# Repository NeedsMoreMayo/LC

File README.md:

# LC meter
The LC meter in this project is based on a popular design that's found on numerous websites. I added an external GPSDO input to use as stable clock reference and a second input so the meter can be used as a frequency counter.

## Principle of operation

## Major components
- The display is a 1602A (ver 5.5) with an I2C PCF8574 expander from aliExpress.
- uC is AVR32DB28

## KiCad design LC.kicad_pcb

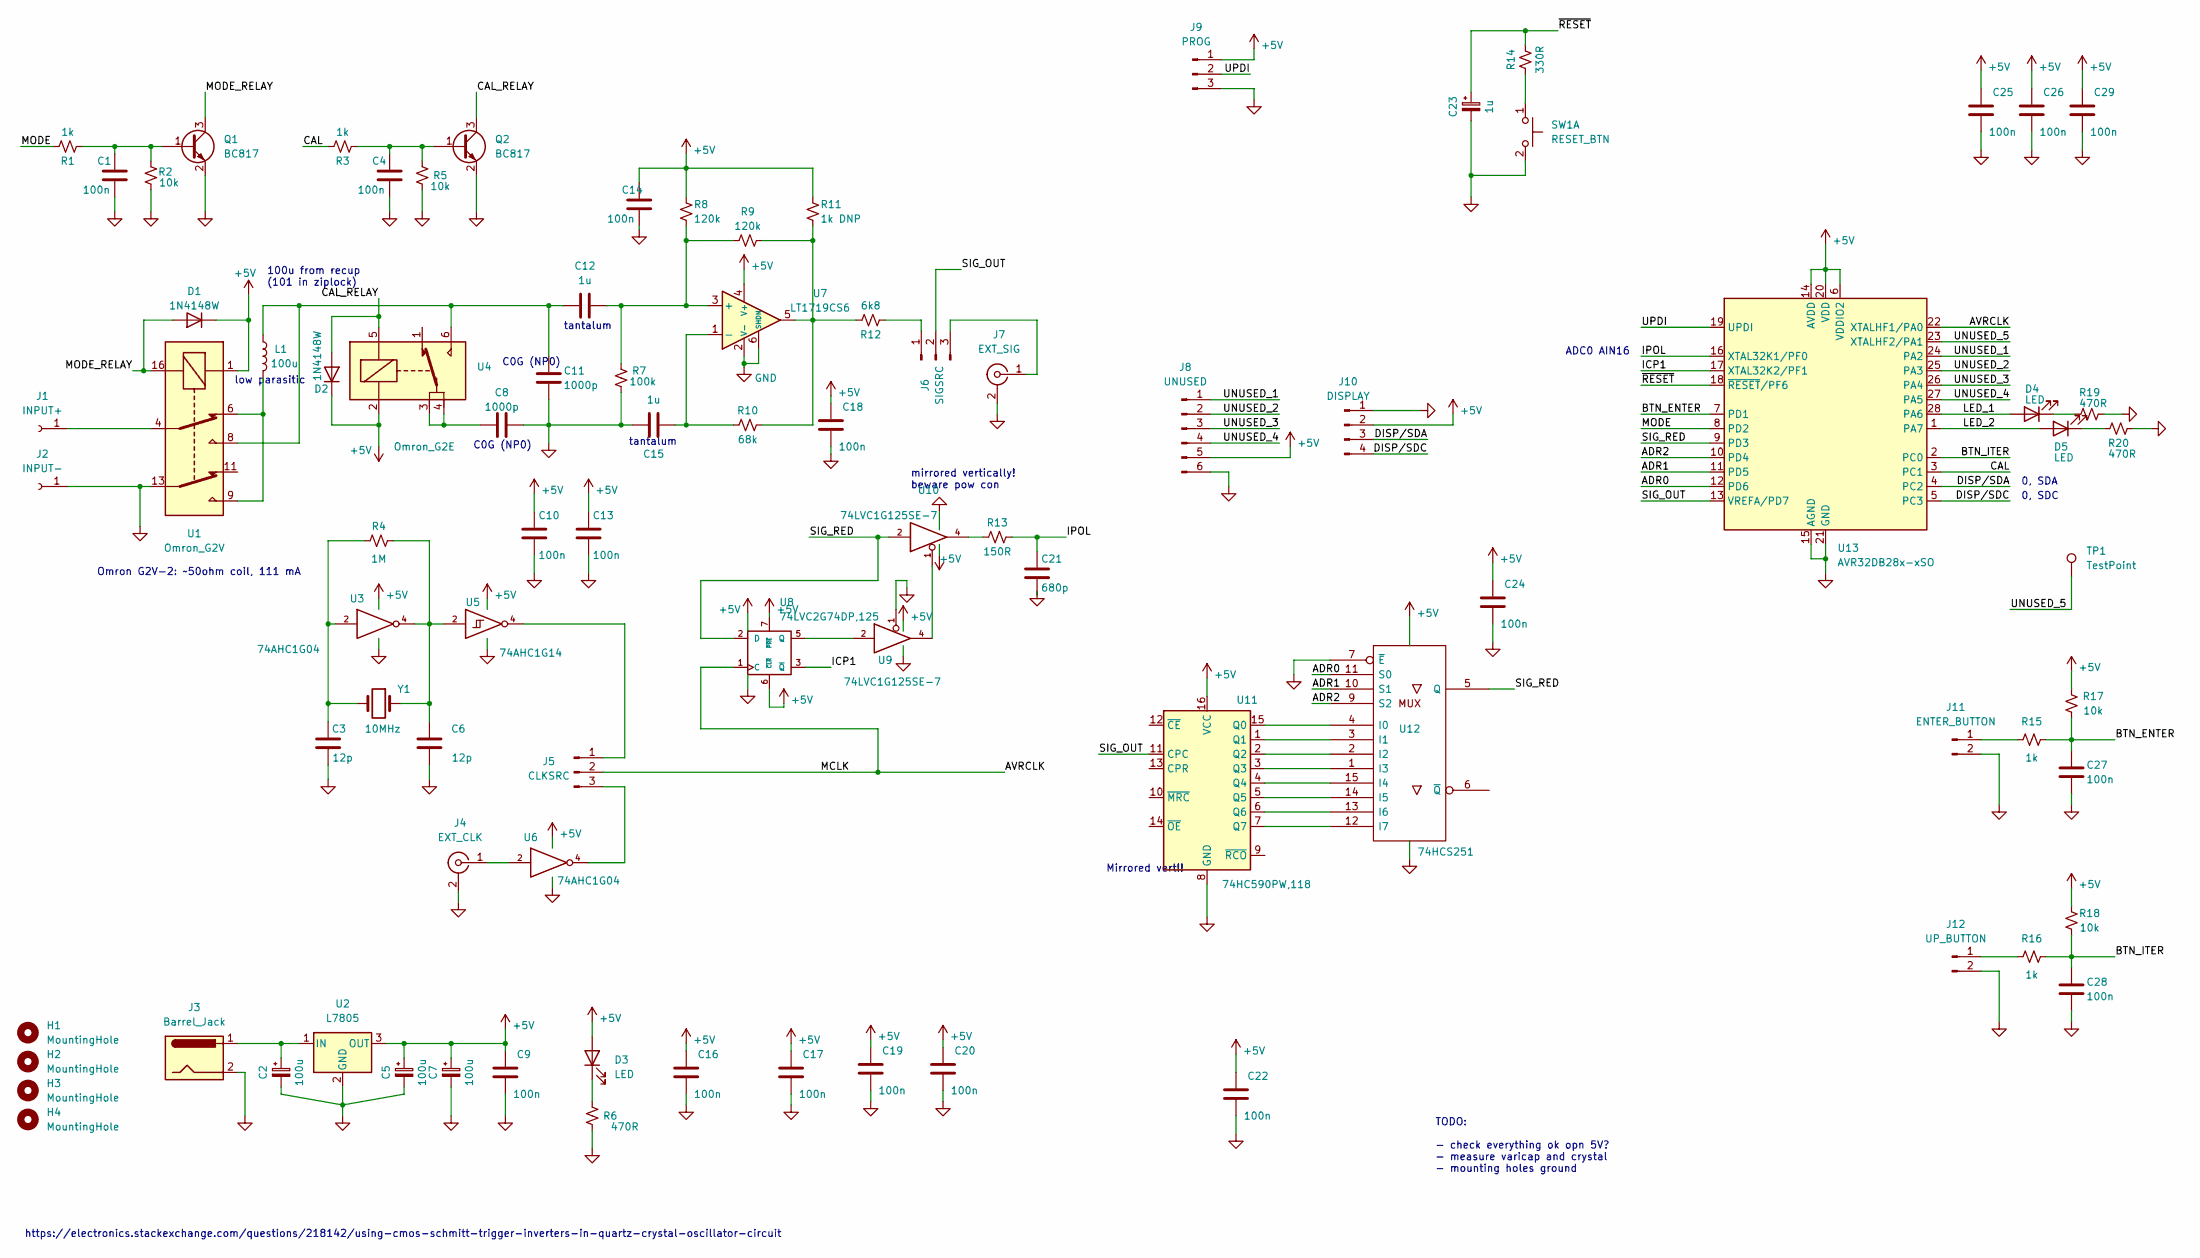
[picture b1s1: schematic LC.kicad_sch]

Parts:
C1, C4, C9, C10, C13, C14, C16, C17, C18, C19, C20, C22, C24, C25, C26, C27, C28, C29: 100n; C_0805_2012Metric_Pad1.18x1.45mm_HandSolder
C2, C5, C7: 100u; CP_Radial_D5.0mm_P2.00mm
C3, C6: 12p; C_0805_2012Metric_Pad1.18x1.45mm_HandSolder
C8, C11: 1000p; C_0805_2012Metric_Pad1.18x1.45mm_HandSolder
C12, C15, C23: 1u; C_0805_2012Metric_Pad1.18x1.45mm_HandSolder
C21: 680p; C_0805_2012Metric_Pad1.18x1.45mm_HandSolder
D1, D2: 1N4148W; D_SOD-123
D3, D4, D5: LED; LED_1206_3216Metric
H1, H2, H3, H4: MountingHole; MountingHole_3.2mm_M3_Pad
J1: INPUT+; Pin_D1.0mm_L10.0mm
J2: INPUT-; Pin_D1.0mm_L10.0mm
J3: Barrel_Jack; BarrelJack_GCT_DCJ200-10-A_Horizontal
J4: EXT_CLK; U.FL_Molex_MCRF_73412-0110_Vertical
J5: CLKSRC; PinHeader_1x03_P2.54mm_Vertical
J6: SIGSRC; PinHeader_1x03_P2.54mm_Vertical
J7: EXT_SIG; U.FL_Molex_MCRF_73412-0110_Vertical
J8: UNUSED; PinHeader_2x03_P2.54mm_Vertical
J9: PROG; PinHeader_1x03_P2.54mm_Vertical
J10: DISPLAY; PinHeader_1x04_P2.54mm_Vertical
J11: ENTER_BUTTON; PinHeader_1x02_P2.54mm_Vertical
J12: UP_BUTTON; PinHeader_1x02_P2.54mm_Vertical
L1: 100u; L_Coilcraft_LPS5030
Q1, Q2: BC817; SOT-23
R1, R3, R15, R16: 1k; R_0805_2012Metric_Pad1.20x1.40mm_HandSolder
R2, R5, R17, R18: 10k; R_0805_2012Metric_Pad1.20x1.40mm_HandSolder
R4: 1M; R_0805_2012Metric_Pad1.20x1.40mm_HandSolder
R6, R19, R20: 470R; R_0805_2012Metric_Pad1.20x1.40mm_HandSolder
R7: 100k; R_0805_2012Metric_Pad1.20x1.40mm_HandSolder
R8, R9: 120k; R_0805_2012Metric_Pad1.20x1.40mm_HandSolder
R10: 68k; R_0805_2012Metric_Pad1.20x1.40mm_HandSolder
R11: 1k DNP; R_0805_2012Metric_Pad1.20x1.40mm_HandSolder
R12: 6k8; R_0805_2012Metric_Pad1.20x1.40mm_HandSolder
R13: 150R; R_0805_2012Metric_Pad1.20x1.40mm_HandSolder
R14: 330R; R_0805_2012Metric_Pad1.20x1.40mm_HandSolder
SW1: RESET_BTN; BUTTON_5X5
TP1: TestPoint; TestPoint_THTPad_1.0x1.0mm_Drill0.5mm
U1: Omron_G2V; Omron G2V-2
U2: L7805; TO-220-3_Vertical
U3, U6: 74AHC1G04; SOT-23-5_HandSoldering
U4: Omron_G2E; Omron G2E
U5: 74AHC1G14; SOT-23-5_HandSoldering
U7: LT1719CS6; SOT-23-6
U8: 74LVC2G74DP,125; TSSOP-8_3x3mm_P0.65mm
U9, U10: 74LVC1G125SE-7; SOT-353_SC-70-5
U11: 74HC590PW,118; TSSOP-16_4.4x5mm_P0.65mm
U12: 74HCS251; SOIC-16_4.55x10.3mm_P1.27mm
U13: AVR32DB28x-xSO; SOIC-28W_7.5x17.9mm_P1.27mm
Y1: 10MHz; Crystal_HC49-4H_Vertical

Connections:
+5V: C5.1, C7.1, C9.2, C10.2, C13.2, C14.2, C16.2, C17.2, C18.2, C19.2, C20.2, C22.2, C24.2, C25.2, C26.2, C29.2, D1.1 (K), D2.1 (K), D3.2 (A), J8.5, J9.1, J10.2, R8.2, R11.2, R17.1, R18.1, U1.1, U2.3 (OUT), U3.5 (VCC), U4.2, U5.5 (VCC), U6.5 (VCC), U7.4 (V+), U8.6 (~CLR), U8.7 (~PRE), U8.8 (VCC), U9.5 (VCC), U10.5 (VCC), U11.16 (VCC), U12.16 (VCC), U13.6 (VDDIO2), U13.14 (AVDD), U13.20 (VDD)
/ADR0: U12.11 (S0), U13.12 (PD6)
/ADR1: U12.10 (S1), U13.11 (PD5)
/ADR2: U12.9 (S2), U13.10 (PD4)
/AVRCLK: J5.2, U8.1 (C), U13.22 (XTALHF1/PA0)
/BTN_ENTER: C27.2, R15.2, R17.2, U13.7 (PD1)
/BTN_ITER: C28.2, R16.2, R18.2, U13.2 (PC0)
/CAL: R3.2, U13.3 (PC1)
/CAL_RELAY: D2.2 (A), Q2.3 (C), U4.5
/DISP/SDA: J10.3, U13.4 (PC2)
/DISP/SDC: J10.4, U13.5 (PC3)
/ICP1: U8.3 (~Q), U13.17 (XTAL32K2/PF1)
/IPOL: C21.2, R13.1, U13.16 (XTAL32K1/PF0)
/LED_1: D4.2 (A), U13.28 (PA6)
/LED_2: D5.2 (A), U13.1 (PA7)
/MODE: R1.2, U13.8 (PD2)
/MODE_RELAY: D1.2 (A), Q1.3 (C), U1.16
/SIG_OUT: J6.2, U11.11 (CPC), U13.13 (VREFA/PD7)
/SIG_RED: U8.2 (D), U10.2, U12.5 (Q), U13.9 (PD3)
/UNUSED_1: J8.1, U13.24 (PA2)
/UNUSED_2: J8.2, U13.25 (PA3)
/UNUSED_3: J8.3, U13.26 (PA4)
/UNUSED_4: J8.4, U13.27 (PA5)
/UNUSED_5: TP1.1, U13.23 (XTALHF2/PA1)
/UPDI: J9.2, U13.19 (UPDI)
/~RESET: C23.1, R14.2, U13.18 (~RESET/PF6)
GND: C1.1, C2.2, C3.2, C4.1, C5.2, C6.2, C7.2, C8.1, C9.1, C10.1, C11.1, C13.1, C14.1, C15.1, C16.1, C17.1, C18.1, C19.1, C20.1, C21.1, C22.1, C23.2, C24.1, C25.1, C26.1, C27.1, C28.1, C29.1, J2.1, J3.2, J4.2 (Ext), J7.2 (Ext), J8.6, J9.3, J10.1, J11.2, J12.2, Q1.2 (E), Q2.2 (E), R2.2, R5.2, R6.2, R7.1, R19.2, R20.2, SW1.2 (D), U1.13, U2.2 (GND), U3.3 (GND), U5.3 (GND), U6.3 (GND), U7.2 (V-), U7.6 (SHDN), U8.4 (GND), U9.1, U9.3 (GND), U10.3 (GND), U11.8 (GND), U12.7 (~E), U12.8 (GND), U13.15 (AGND), U13.21 (GND)
unnamed: C1.2, Q1.1 (B), R1.1, R2.1
unnamed: C2.1, J3.1, U2.1 (IN)
unnamed: C3.1, R4.1, U3.2, Y1.2
unnamed: C4.2, Q2.1 (B), R3.1, R5.1
unnamed: C6.1, R4.2, U3.4, U5.2, Y1.1
unnamed: C8.2, U4.3, U4.4
unnamed: C11.2, C12.1, L1.1, U1.8, U4.6
unnamed: C12.2, R7.2, R8.1, R9.1, U7.3 (+)
unnamed: C15.2, R10.1, U7.1 (-)
unnamed: D3.1 (K), R6.1
unnamed: D4.1 (K), R19.1
unnamed: D5.1 (K), R20.1
unnamed: J1.1, U1.4
unnamed: J4.1 (In), U6.2
unnamed: J5.1, U5.4
unnamed: J5.3, U6.4
unnamed: J6.1, R12.1
unnamed: J6.3, J7.1 (In)
unnamed: J11.1, R15.1
unnamed: J12.1, R16.1
unnamed: L1.2, U1.6, U1.9
unnamed: R9.2, R10.2, R11.1, R12.2, U7.5
unnamed: R13.2, U10.4
unnamed: R14.1, SW1.1 (C)
unnamed: U8.5 (Q), U9.2
unnamed: U9.4, U10.1
unnamed: U11.1 (Q1), U12.3 (I1)
unnamed: U11.2 (Q2), U12.2 (I2)
unnamed: U11.3 (Q3), U12.1 (I3)
unnamed: U11.4 (Q4), U12.15 (I4)
unnamed: U11.5 (Q5), U12.14 (I5)
unnamed: U11.6 (Q6), U12.13 (I6)
unnamed: U11.7 (Q7), U12.12 (I7)
unnamed: U11.15 (Q0), U12.4 (I0)

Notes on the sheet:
100u from recup (101 in ziplock)
C0G (NP0)
mirrored vertically! beware pow con
low parasitic
0, SDC
TODO: - check everything ok opn 5V? - measure varicap and crystal - mounting holes ground
tantalum
Mirrored vert!!
Omron G2V-2: ~50ohm coil, 111 mA
ADC0 AIN16
0, SDA
https://electronics.stackexchange.com/questions/218142/using-cmos-schmitt-trigger-inverters-in-quartz-crystal-oscillator-circuit

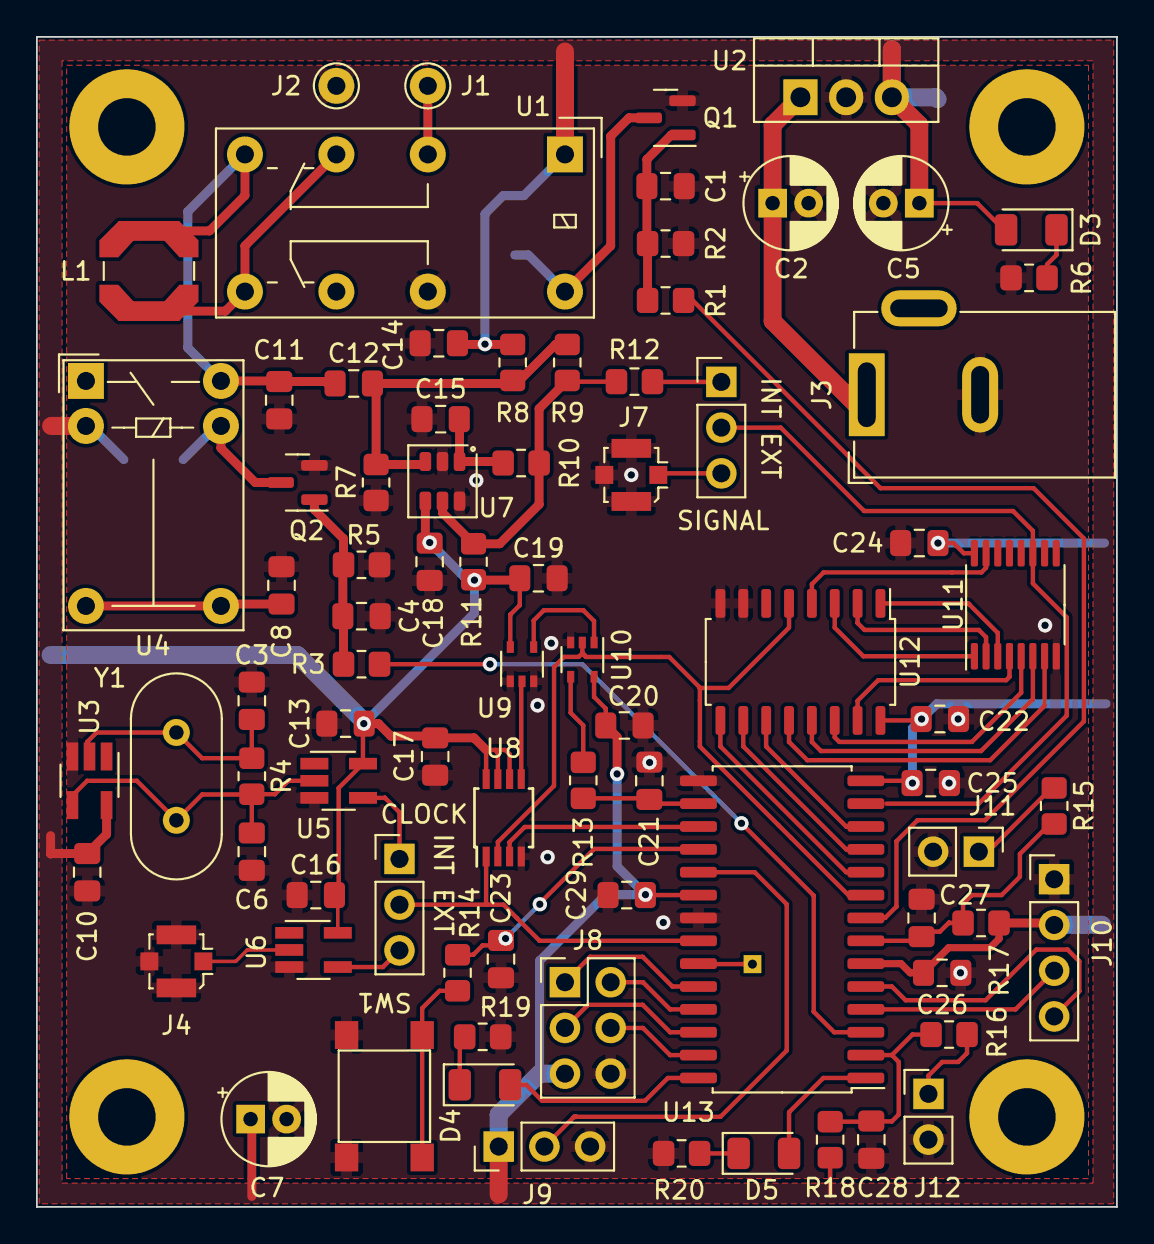
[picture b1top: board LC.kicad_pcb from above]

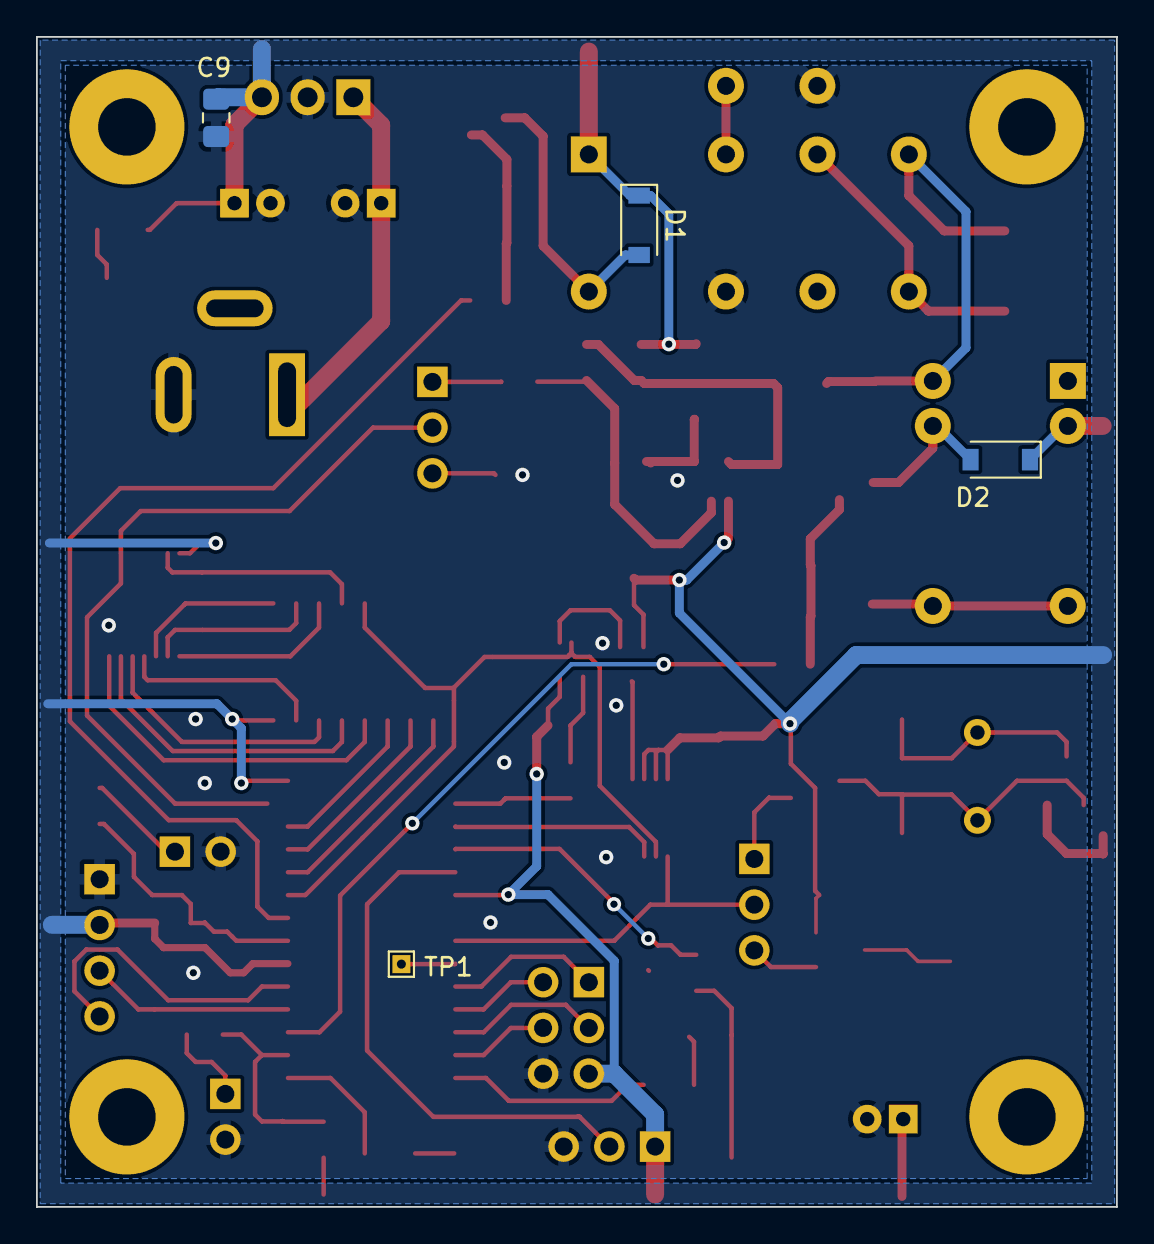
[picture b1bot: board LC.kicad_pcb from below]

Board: 2 copper layers, 60.0 x 65.0 mm, 89 parts (4 on the bottom side), 61 nets.

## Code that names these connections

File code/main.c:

//F_CPU defined in makefile
//#define F_CPU 10000000ul

#include <avr/io.h>
#include <util/delay.h>		//temporary sin
#include <avr/interrupt.h>
//#include <math.h>

#include "LCD.h"


//PORT A
#define AVRCLK_PIN		0
#define CAL_PIN			1
#define UNUSED_1_PIN	2
#define UNUSED_2_PIN	3
#define UNUSED_3_PIN	4
#define UNUSED_4_PIN	5
#define LED_1_PIN		6
#define LED_2_PIN		7

//PORT C
#define BTN_ITER_PIN	0
#define UNUSED_5_PIN	1
#define DISP_SDA_PIN	2
#define DISP_SDC_PIN	3

//PORT D
#define BTN_ENTER_PIN	1	//ADC0 AIN1
#define MODE_PIN		2
#define SIG_RED_PIN		3
#define ADR2_PIN		4
#define ADR1_PIN		5
#define ADR0_PIN		6
#define SIG_OUT_PIN		7

//PORT F
#define IPOL_PIN		0
#define ICP1_PIN		1
#define RESET_PIN		6

void PORTS_init(void);
void I2C0_init(void);
void LCD_init(void);
void TOGGLE_LED(void);

int main(void){
	cli(); //disable interrupts when enabling interrupt handlers
	PORTS_init();
	I2C0_init();
	LCD_init();
	sei();//enable interrupts
    while (1){
		TOGGLE_LED();
		_delay_ms(1000);

		LCD1602_send_command(CLEAR_DISPLAY);
		_delay_us(100);
		LCD1602_send_command(RETURN_HOME);
		_delay_us(100);
		LCD1602_send_string("Testing 123");
		_delay_us(100);
    }
}


void TOGGLE_LED(){
	PORTD.OUTTGL = (1 << LED_1_PIN)
		 		|  (1 << LED_2_PIN);
}

void PORTS_init(){
	//CAL, LED_1 and LED_2 are output on PORTA
	PORTA.DIR =   (1 << CAL_PIN)
				| (1 << LED_1_PIN)
				| (1 << LED_2_PIN);
	PORTA.OUT = 0x00;
	
	//DISP_SDA and DISP_SDC are output on PORTC
	PORTC.DIR =   (1 << DISP_SDA_PIN)
				| (1 << DISP_SDC_PIN);
	PORTC.OUT = 0x00;
	
	//MODE and ADR0..2 are output on PORTD
	PORTD.DIR =   (1 << MODE_PIN)
				| (1 << ADR0_PIN)
				| (1 << ADR1_PIN)
				| (1 << ADR2_PIN);
	PORTD.OUT = 0x00;
	
	//no output on PORTD
	PORTF.DIR = 0;
	PORTF.OUT = 0x00;
}

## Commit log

2024-02-02 update display connector
2024-02-02 Unused IO to connector and LCD connector
2024-02-03 update gitignore and init code
2024-02-03 changed comparator: LM311 became TLV3201
2024-02-03 R11 is Do Not Populate
2024-02-04 Initial LCD code, tested on different platform
2024-02-04 Updated comparator oscillator with LTSpice simulation results
    LT1719 operates nicely, but some values need to be adjusted. Especially the coupling caps need to be changed (10u -> 1u) so I decided to change them to MLCC.
2024-02-04 Updated schematic for 5V devices in TIC, PCB is in todo
2024-02-05 Updated schematic with correct 5V devices
2024-02-05 forgot that polystyrene are THT
2024-02-05 a few more pin swaps
